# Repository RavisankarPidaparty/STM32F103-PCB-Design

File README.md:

# STM32F103-PCB-Design
This PCB board is a development board created using Kicad a free open source design tool. this PCB design consists of an STM32F103 IC.

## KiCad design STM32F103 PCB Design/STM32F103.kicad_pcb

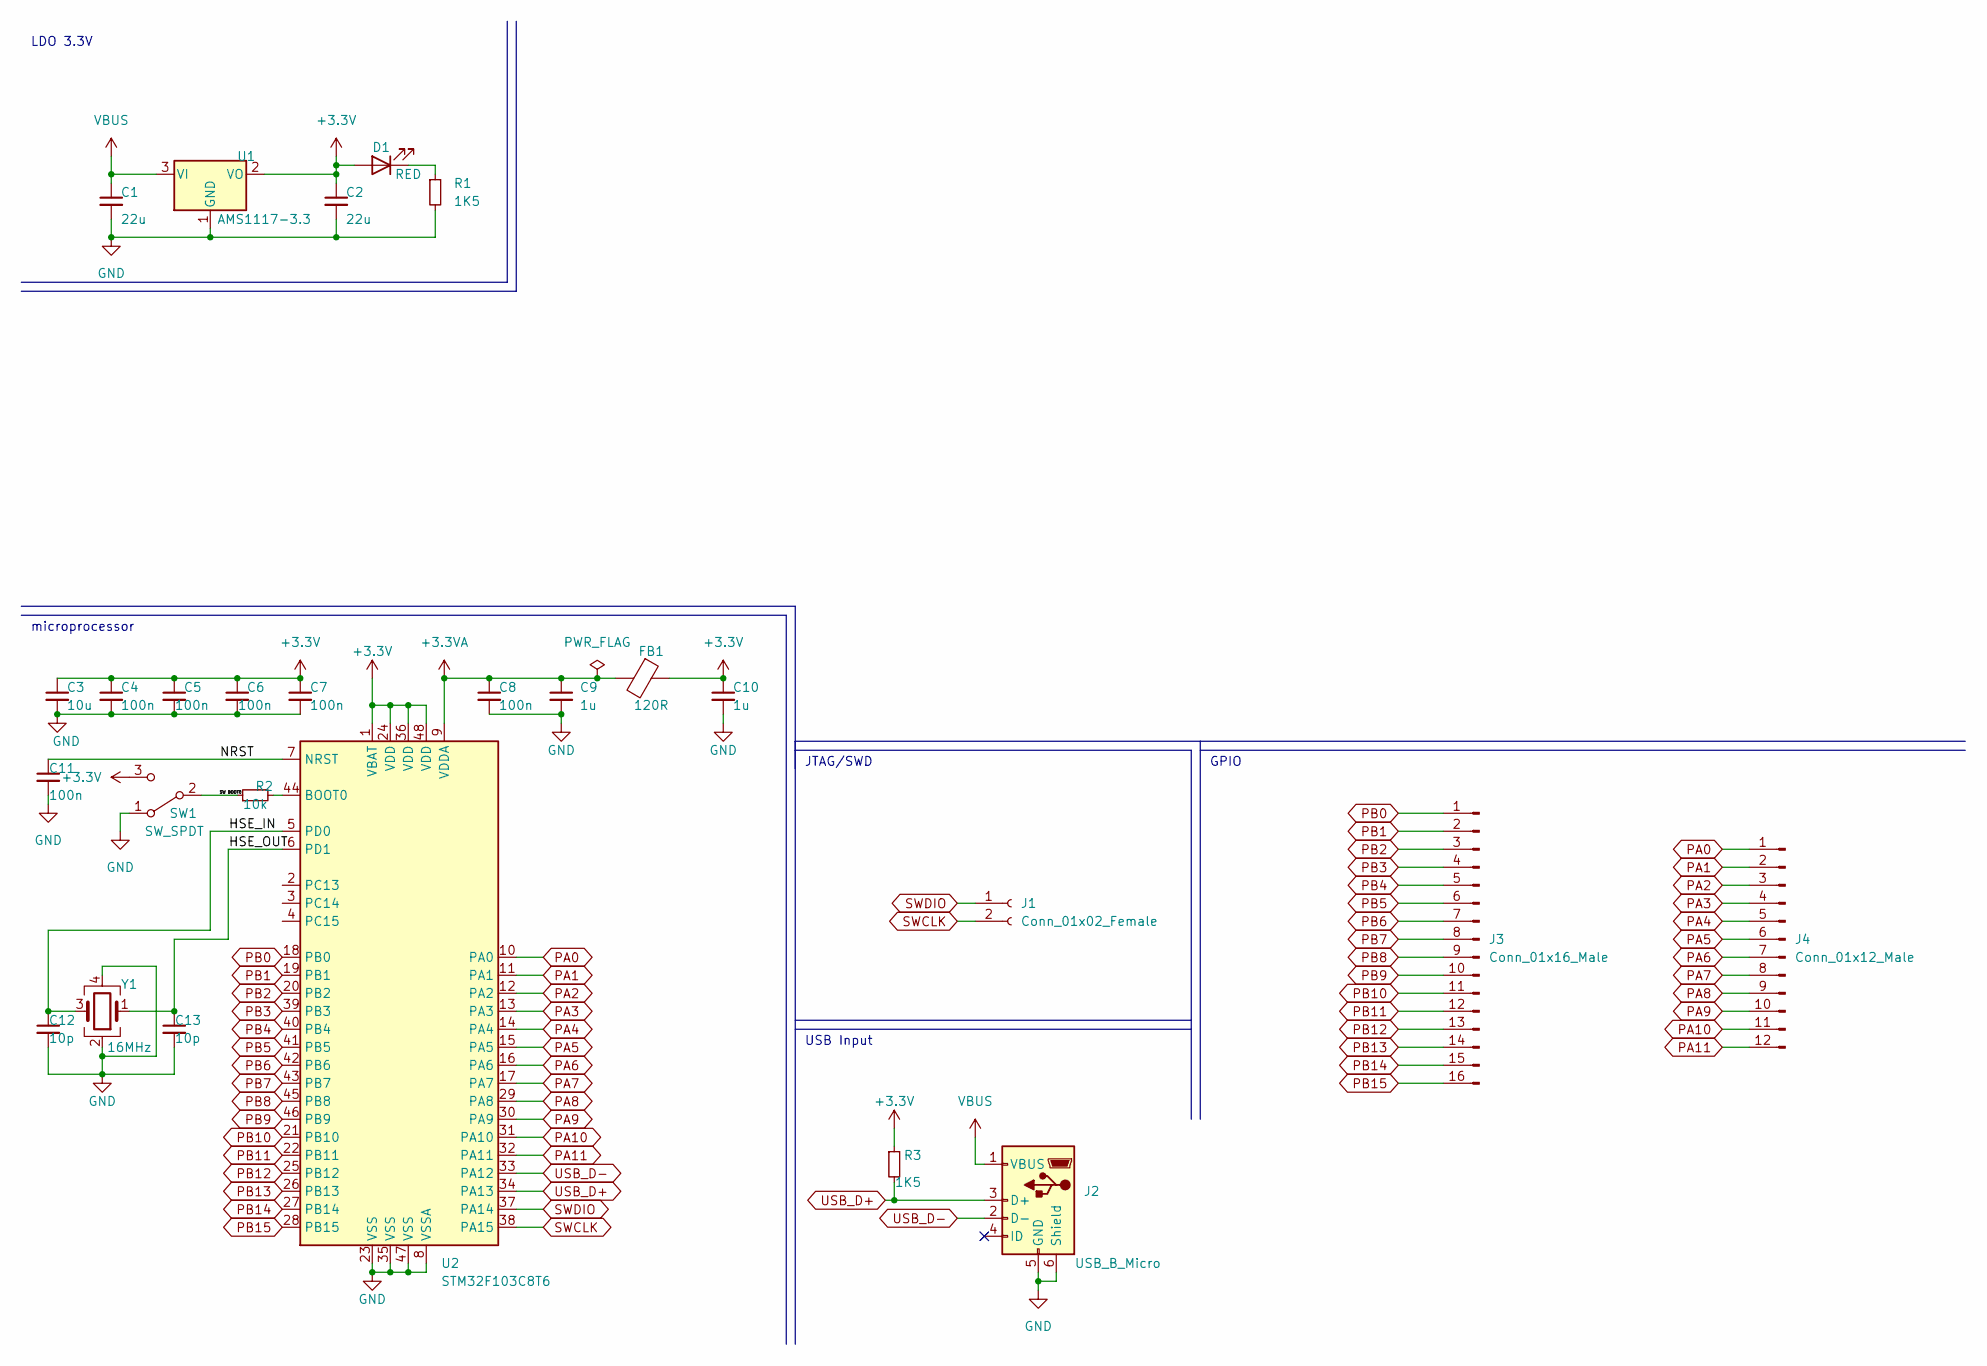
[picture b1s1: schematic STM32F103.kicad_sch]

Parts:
C1, C2: 22u; C_0402_1005Metric
C3: 10u; C_0402_1005Metric
C4, C5, C6, C7, C8, C11: 100n; C_0402_1005Metric
C9, C10: 1u; C_0402_1005Metric
C12, C13: 10p; C_0402_1005Metric
D1: RED; LED_0201_0603Metric
FB1: 120R; L_0402_1005Metric
J1: Conn_01x02_Female; PinHeader_1x02_P2.54mm_Vertical
J2: USB_B_Micro; USB_Micro-B_Wuerth_629105150521
J3: Conn_01x16_Male; PinSocket_1x16_P2.54mm_Vertical
J4: Conn_01x12_Male; PinSocket_1x12_P2.54mm_Vertical
R1, R3: 1K5; R_0402_1005Metric
R2: 10k; R_0402_1005Metric
SW1: SW_SPDT; SW_SPDT_PCM12
U1: AMS1117-3.3; SOT-223-3_TabPin2
U2: STM32F103C8T6; LQFP-48_7x7mm_P0.5mm
Y1: 16MHz; Crystal_SMD_3225-4Pin_3.2x2.5mm

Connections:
+3.3V: C2.1, C3.1, C4.1, C5.1, C6.1, C7.1, C10.1, D1.2 (A), FB1.1, R3.1, SW1.3 (C), U1.2 (VO), U2.1 (VBAT), U2.24 (VDD), U2.36 (VDD), U2.48 (VDD)
+3.3VA: C8.1, C9.1, FB1.2, U2.9 (VDDA)
/HSE_IN: C12.1, U2.5 (PD0), Y1.3
/HSE_OUT: C13.1, U2.6 (PD1), Y1.1
/NRST: C11.1, U2.7 (NRST)
/SW BOOT0: R2.1, SW1.2 (B)
GND: C1.2, C2.2, C3.2, C4.2, C5.2, C6.2, C7.2, C8.2, C9.2, C10.2, C11.2, C12.2, C13.2, J2.5 (GND), J2.6 (Shield), R1.2, SW1.1 (A), U1.1 (GND), U2.8 (VSSA), U2.23 (VSS), U2.35 (VSS), U2.47 (VSS), Y1.2, Y1.4
unnamed: D1.1 (K), R1.1
unnamed: R2.2, U2.44 (BOOT0)
PA0: J4.1, U2.10 (PA0)
PA1: J4.2, U2.11 (PA1)
PA2: J4.3, U2.12 (PA2)
PA3: J4.4, U2.13 (PA3)
PA4: J4.5, U2.14 (PA4)
PA5: J4.6, U2.15 (PA5)
PA6: J4.7, U2.16 (PA6)
PA7: J4.8, U2.17 (PA7)
PA8: J4.9, U2.29 (PA8)
PA9: J4.10, U2.30 (PA9)
PA10: J4.11, U2.31 (PA10)
PA11: J4.12, U2.32 (PA11)
PB0: J3.1, U2.18 (PB0)
PB1: J3.2, U2.19 (PB1)
PB2: J3.3, U2.20 (PB2)
PB3: J3.4, U2.39 (PB3)
PB4: J3.5, U2.40 (PB4)
PB5: J3.6, U2.41 (PB5)
PB6: J3.7, U2.42 (PB6)
PB7: J3.8, U2.43 (PB7)
PB8: J3.9, U2.45 (PB8)
PB9: J3.10, U2.46 (PB9)
PB10: J3.11, U2.21 (PB10)
PB11: J3.12, U2.22 (PB11)
PB12: J3.13, U2.25 (PB12)
PB13: J3.14, U2.26 (PB13)
PB14: J3.15, U2.27 (PB14)
PB15: J3.16, U2.28 (PB15)
SWCLK: J1.2, U2.38 (PA15)
SWDIO: J1.1, U2.37 (PA14)
USB_D+: J2.3 (D+), R3.2, U2.34 (PA13)
USB_D-: J2.2 (D-), U2.33 (PA12)
VBUS: C1.1, J2.1 (VBUS), U1.3 (VI)

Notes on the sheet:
LDO 3.3V
microprocessor
JTAG/SWD
GPIO
USB Input

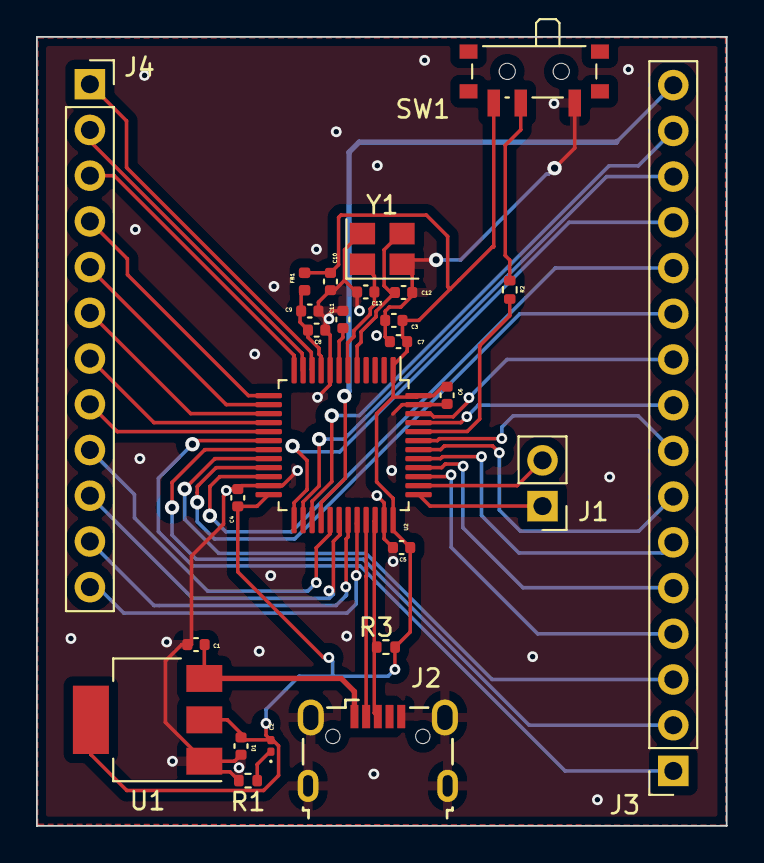
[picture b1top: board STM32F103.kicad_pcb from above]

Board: 2 copper layers, 38.3 x 43.8 mm, 26 parts (0 on the bottom side), 42 nets.
